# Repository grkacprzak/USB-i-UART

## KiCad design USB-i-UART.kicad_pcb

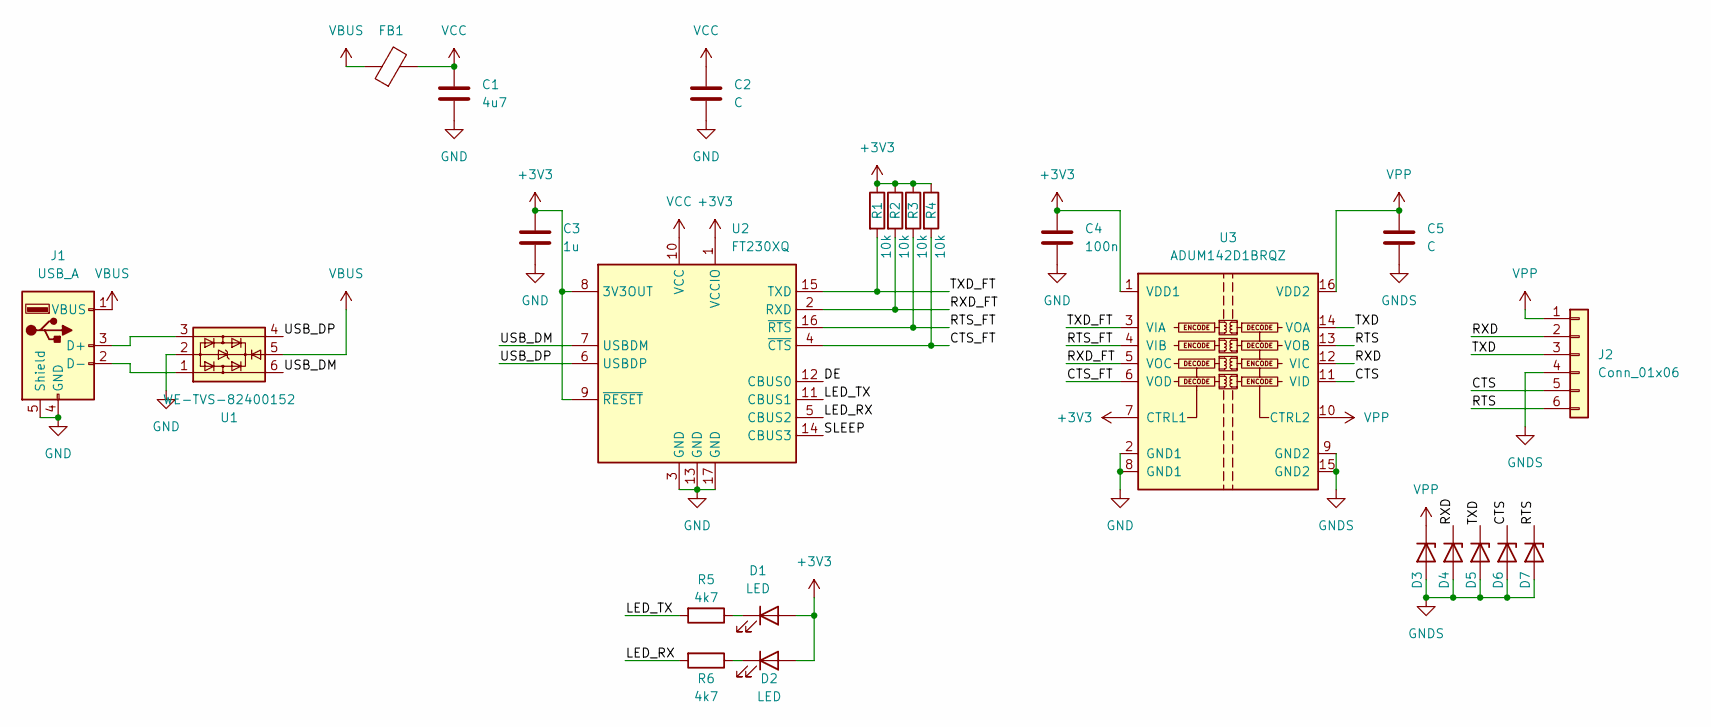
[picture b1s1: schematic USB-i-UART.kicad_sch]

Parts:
C1: 4u7; C_0402_1005Metric
C2, C5: C; C_0402_1005Metric
C3: 1u; C_0402_1005Metric
C4: 100n; C_0402_1005Metric
D1, D2: LED; LED_0603_1608Metric
D3, D4, D5, D6, D7: D_Zener; D_SOD-523
FB1: FerriteBead; L_0402_1005Metric
J1: USB_A; USB3_A_Molex_480371000_Plug
J2: Conn_01x06; PinHeader_1x06_P2.54mm_Horizontal
R1, R2, R3, R4: 10k; R_0402_1005Metric
R5, R6: 4k7; R_0402_1005Metric
U1: WE-TVS-82400152; SOT-563
U2: FT230XQ; QFN-16-1EP_4x4mm_P0.65mm_EP2.1x2.1mm
U3: ADUM142D1BRQZ; SSOP-16_3.9x4.9mm_P0.635mm

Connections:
+3V3: C3.1, C4.1, D1.2 (A), D2.2 (A), R1.1, R2.1, R3.1, R4.1, U2.1 (VCCIO), U2.8 (3V3OUT), U2.9 (~RESET), U3.1 (VDD1), U3.7 (CTRL1)
/CTS: D6.1 (K), J2.5, U3.11 (VID)
/CTS_FT: R4.2, U2.4 (~CTS), U3.6 (VOD)
/DE: U2.12 (CBUS0)
/LED_RX: R6.2, U2.5 (CBUS2)
/LED_TX: R5.2, U2.11 (CBUS1)
/RTS: D7.1 (K), J2.6, U3.13 (VOB)
/RTS_FT: R3.2, U2.16 (~RTS), U3.4 (VIB)
/RXD: D4.1 (K), J2.2, U3.12 (VIC)
/RXD_FT: R2.2, U2.2 (RXD), U3.5 (VOC)
/SLEEP: U2.14 (CBUS3)
/TXD: D5.1 (K), J2.3, U3.14 (VOA)
/TXD_FT: R1.2, U2.15 (TXD), U3.3 (VIA)
/USB_DM: U1.6, U2.7 (USBDM)
/USB_DP: U1.4, U2.6 (USBDP)
GND: C1.2, C2.2, C3.2, C4.2, J1.4 (GND), J1.5 (Shield), U1.2, U2.3 (GND), U2.13 (GND), U2.17 (GND), U3.2 (GND1), U3.8 (GND1)
GNDS: C5.2, D3.2 (A), D4.2 (A), D5.2 (A), D6.2 (A), D7.2 (A), J2.4, U3.9 (GND2), U3.15 (GND2)
unnamed: D1.1 (K), R5.1
unnamed: D2.1 (K), R6.1
unnamed: J1.3 (D+), U1.3
unnamed: J1.2 (D-), U1.1
VBUS: FB1.1, J1.1 (VBUS), U1.5
VCC: C1.1, C2.1, FB1.2, U2.10 (VCC)
VPP: C5.1, D3.1 (K), J2.1, U3.10 (CTRL2), U3.16 (VDD2)

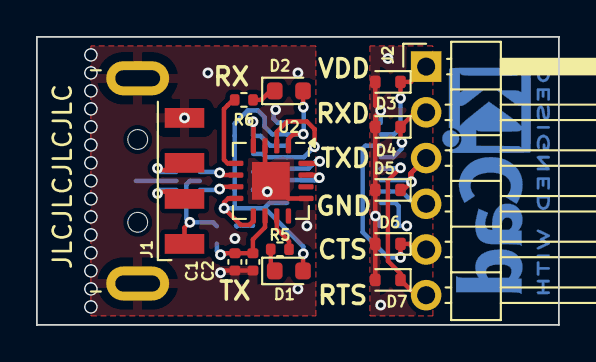
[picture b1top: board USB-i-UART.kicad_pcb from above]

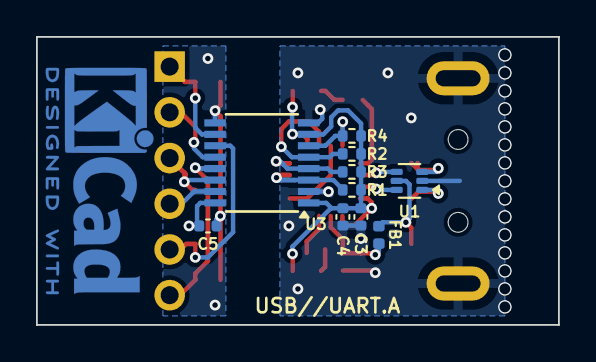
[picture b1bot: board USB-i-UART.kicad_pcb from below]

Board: 4 copper layers, 29.0 x 16.0 mm, 24 parts (10 on the bottom side), 22 nets.
